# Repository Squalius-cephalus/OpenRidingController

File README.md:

# OpenRidingController
A horse riding game controller for the PC/Mac. The idea is to emulate basic horse riding behaviors and converts those to work a variety of video games.

The controller mainly uses **RP2040 Zero**, **TCRT5000** IR modules and 3D printed parts. Code uses **[CircuitPython 10](https://circuitpython.org/board/waveshare_rp2040_zero/)** for fast prototyping, later revisions may move to Arduino C or something similar.

Currently the controller can emulate keyboard, mouse and DirectInput controller, however, this wont work on any "keyboard to game console" adapter, because of how the USB composite system works.
## Revision 2
Latest revision uses a PCB, and the goal is to minimize the number of 3D printed parts. Strirrups uses an IMU sensors, so controller can be adapted to different frames easily.

Build guide and BOM in the works.

## Revision 1
Handwired design, frame, sensors etc uses many 3D printed parts. Not in active develoment. 

## Video

## Hardware Required

 - RP2040 Zero
 - 4 pcs TCRT5000 Infrared Reflective Sensor (with analog out)
 - [3D Printed parts, steel pipes and M3 hardware](https://github.com/Squalius-cephalus/OpenRidingController/tree/main/3D_files)

## Required Libraries

 - [Adafruit CircuitPython HID Library](https://github.com/adafruit/Adafruit_CircuitPython_HID/tree/main)
 - [Adafruit CircuitPython Nunchuk](https://github.com/adafruit/Adafruit_CircuitPython_Nunchuk)
 - Adafruit Neopixel
 - Bus Devices
 - Simple Math

## Circuit Diagram

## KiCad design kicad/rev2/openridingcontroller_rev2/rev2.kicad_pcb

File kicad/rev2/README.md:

## Kicad Footprints

This project uses footprints from various repositories

 - [OLED Display 128x32](https://github.com/crides/kleeb/tree/master/display.pretty)
 - [Nunchuck Connector](https://gitlab.com/phodina/kicad-footprints/-/blob/nintendo/Connector.pretty/Nintendo_Wii_Peripheral_6Pin_Socket_Horizontal.kicad_mod)

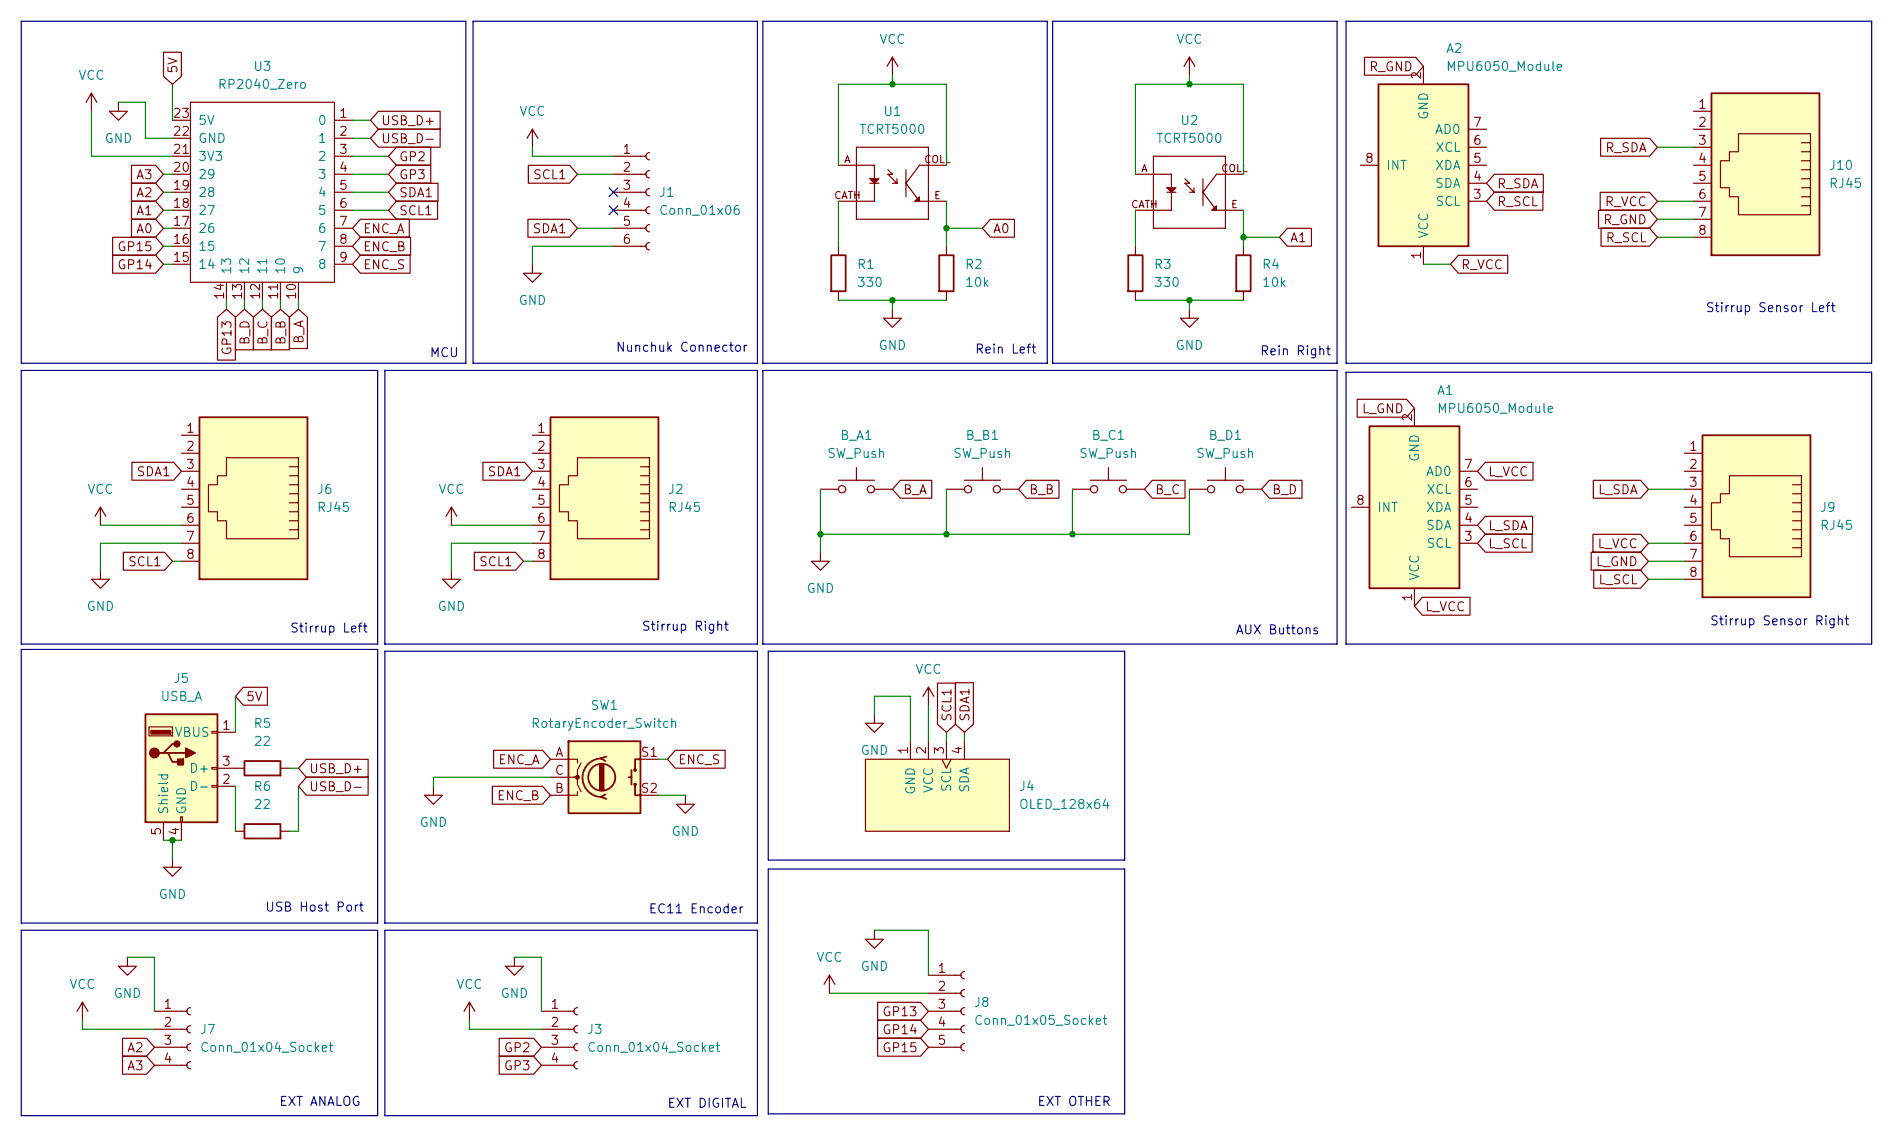
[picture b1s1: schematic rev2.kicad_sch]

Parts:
A1, A2: MPU6050_Module
B_A1: SW_Push; SW_PUSH_6mm_H5mm
B_B1: SW_Push; SW_PUSH_6mm_H5mm
B_C1: SW_Push; SW_PUSH_6mm_H5mm
B_D1: SW_Push; SW_PUSH_6mm_H5mm
J1: Conn_01x06; Nintendo_Wii_Peripheral_5Pin_Card_edge
J2, J6, J9, J10: RJ45; RJ45_OST_PJ012-8P8CX_Vertical
J3, J7: Conn_01x04_Socket; PinHeader_1x04_P2.54mm_Vertical
J4: OLED_128x64
J5: USB_A; USB_A_Molex_67643_Horizontal
J8: Conn_01x05_Socket; PinHeader_1x05_P2.54mm_Vertical
R1, R3: 330; R_Axial_DIN0204_L3.6mm_D1.6mm_P7.62mm_Horizontal
R2, R4: 10k; R_Axial_DIN0204_L3.6mm_D1.6mm_P7.62mm_Horizontal
R5, R6: 22; R_Axial_DIN0204_L3.6mm_D1.6mm_P7.62mm_Horizontal
SW1: RotaryEncoder_Switch; RotaryEncoder_Alps_EC11E-Switch_Vertical_H20mm
U1, U2: TCRT5000; OPTO_TCRT5000; PARTREV 1.7
U3: RP2040_Zero

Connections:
5V: J5.1 (VBUS), U3.23 (5V)
A0: R2.1, U1.E, U3.17 (26)
A1: R4.1, U2.E, U3.18 (27)
A2: J7.3, U3.19 (28)
A3: J7.4, U3.20 (29)
B_A: B_A1.2, U3.10 (9)
B_B: B_B1.2, U3.11 (10)
B_C: B_C1.2, U3.12 (11)
B_D: B_D1.2, U3.13 (12)
ENC_A: SW1.A, U3.7 (6)
ENC_B: SW1.B, U3.8 (7)
ENC_S: SW1.S1, U3.9 (8)
GND: B_A1.1, B_B1.1, B_C1.1, B_D1.1, J1.6, J2.7, J3.1, J4.1 (GND), J5.4 (GND), J5.5 (Shield), J6.7, J7.1, J8.1, R1.2, R2.2, R3.2, R4.2, SW1.C, SW1.S2, U3.22 (GND)
GP2: J3.3, U3.3 (2)
GP3: J3.4, U3.4 (3)
GP13: J8.3, U3.14 (13)
GP14: J8.4, U3.15 (14)
GP15: J8.5, U3.16 (15)
L_GND: A1.2 (GND), J9.7
L_SCL: A1.3 (SCL), J9.8
L_SDA: A1.4 (SDA), J9.3
L_VCC: A1.1 (VCC), A1.7 (AD0), J9.6
unnamed: J5.3 (D+), R5.1
unnamed: J5.2 (D-), R6.1
unnamed: R1.1, U1.CATH
unnamed: R3.1, U2.CATH
R_GND: A2.2 (GND), J10.7
R_SCL: A2.3 (SCL), J10.8
R_SDA: A2.4 (SDA), J10.3
R_VCC: A2.1 (VCC), J10.6
SCL1: J1.2, J2.8, J4.3 (SCL), J6.8, U3.6 (5)
SDA1: J1.5, J2.3, J4.4 (SDA), J6.3, U3.5 (4)
USB_D+: R5.2, U3.1 (0)
USB_D-: R6.2, U3.2 (1)
VCC: J1.1, J2.6, J3.2, J4.2 (VCC), J6.6, J7.2, J8.2, U1.A, U1.COLL, U2.A, U2.COLL, U3.21 (3V3)

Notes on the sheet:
EXT DIGITAL
USB Host Port
Stirrup Left
AUX Buttons
Rein Right
Stirrup Sensor Right
EC11 Encoder
MCU
EXT OTHER
EXT ANALOG
Stirrup Right
Rein Left
Nunchuk Connector
Stirrup Sensor Left

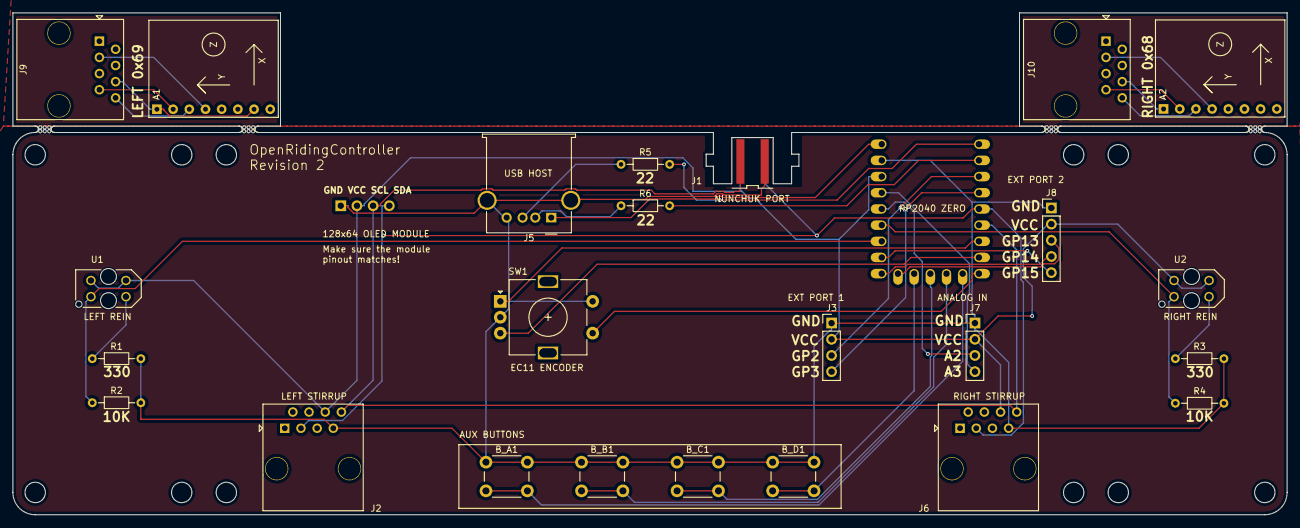
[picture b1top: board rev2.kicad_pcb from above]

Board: 2 copper layers, 200.0 x 78.7 mm, 30 parts (0 on the bottom side), 35 nets.

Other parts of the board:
mouse-bite-1mm-3mm, mouse-bite-1mm-3mm#2, mouse-bite-1mm-3mm#3, mouse-bite-1mm-3mm#4: VAL**; mouse-bite-1mm-3mm

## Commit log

2026-04-10 vitusti kaikkea
2026-04-11 jotain
2026-04-13 Rewrite
2026-04-14 juttuja
2026-04-15 Rewrote almost everything
2026-04-23 Modified the hid_gamepad to support 6 axis instead of 8
2026-04-23 Moved code to own directory, added missing STEP files for the frame
2026-04-23 Added support for Wii Nunchuck controller
2026-04-24 Added basic error handling for nunchuck and flick detection for it
2026-04-25 Moved nunchuck code to own class/file, simpler error handling when nunchuck controller is disconnected
2026-04-26 Controller sends UART data over GP12, can be converted to different game outputs
2026-04-27 Removed unused code, profile reworked and output manager redone
2026-04-27 UART works when controller is not connected to PC
2026-04-30 Removed old profile editor, does not work with new profile format
2026-05-01 Stirrups logic is now much better, needs better calibration. Stirrups and reins input values are now interpolated
2026-05-01 Instead of time based triggers, stirrups uses now speed variable and some thresholds
2026-05-03 Added 3D models for the frame and most of the sensors
2026-05-04 Code optimization, less dictionaries, more classes
2026-05-05 Renaming all the actions etc
2026-05-06 Debug function for later, code optimization, added missing settings and fixed typos
2026-05-07 More CAD files, small bug fixes
2026-05-07 Bug fixes
2026-05-10 Added missing Readme
2026-05-10 UART communication disabled for now
2026-05-11 Added STL files
2026-05-14 Added missing images
2026-05-15 Repository cleanup, fixing "nunchuck" to "nunchuk" and removed UART logic
2026-05-15 Added picture of the controller to the README.md
2026-05-16 Little bit of clone cleanup and added most of missing docstrings
2026-05-23 Fixed that the I2C wont block the USB out, also some small bug fixes
2026-06-12 Moving files and adding missing files for the revision 2.
2026-06-12 Revision 2 code
